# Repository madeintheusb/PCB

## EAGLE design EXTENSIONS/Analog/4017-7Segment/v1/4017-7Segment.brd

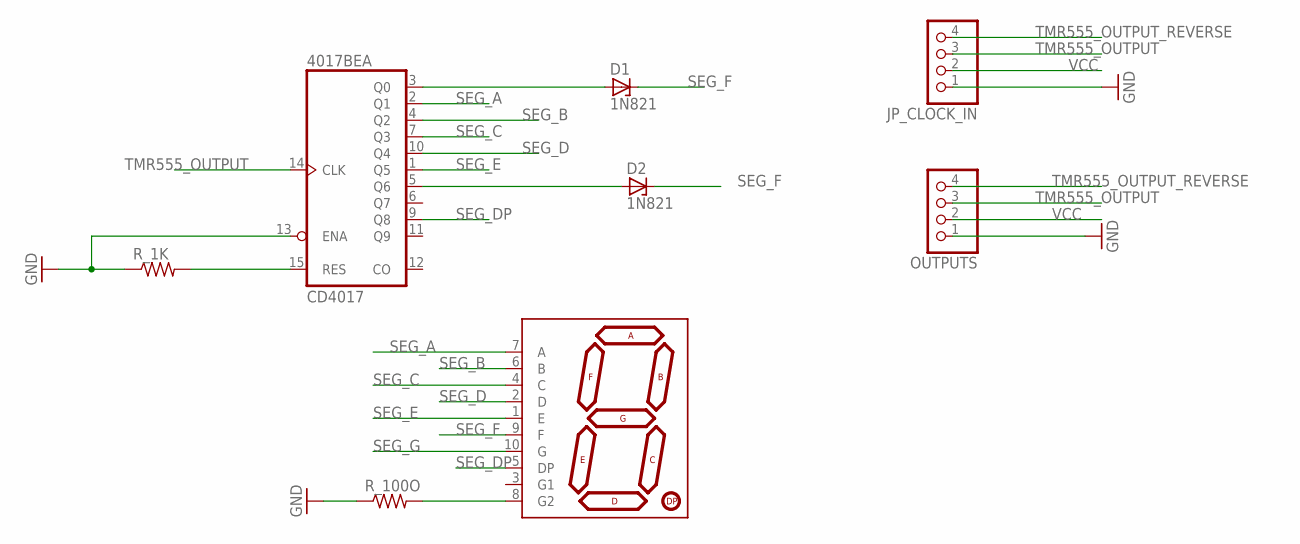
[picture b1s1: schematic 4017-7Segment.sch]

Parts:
4017BE: CD4017; DIL16
D1, D2: 1N821; DO35Z10
JP_CLOCK_IN: PINHD-1X4; 1X04
OUTPUTS: PINHD-1X4; 1X04
R_1K, R_100O: R-US_R1206; R1206
U$1: 7-SEGMENT-DISPLAYPTH; 7-SEGMENT-DISPLAY

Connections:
GND: 4017BE.8 (GND), 4017BE.13 (ENA), JP_CLOCK_IN.1, OUTPUTS.1, R_1K.1, R_100O.1
unnamed: 4017BE.15 (RES), R_1K.2
unnamed: R_100O.2, U$1.8 (G2)
unnamed: 4017BE.3 (Q0), D1.A
unnamed: 4017BE.5 (Q6), D2.A
SEG_A: 4017BE.2 (Q1), U$1.7 (A)
SEG_B: 4017BE.4 (Q2), U$1.6 (B)
SEG_C: 4017BE.7 (Q3), U$1.4 (C)
SEG_D: 4017BE.10 (Q4), U$1.2 (D)
SEG_DP: 4017BE.9 (Q8), U$1.5 (DP)
SEG_E: 4017BE.1 (Q5), U$1.1 (E)
SEG_F: D1.C, D2.C, U$1.9 (F)
SEG_G: U$1.10 (G)
TMR555_OUTPUT: 4017BE.14 (CLK), JP_CLOCK_IN.3, OUTPUTS.3
TMR555_OUTPUT_REVERSE: JP_CLOCK_IN.4, OUTPUTS.4
VCC: 4017BE.16 (VCC), JP_CLOCK_IN.2, OUTPUTS.2

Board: 2 copper layers, 8 parts (0 on the bottom side), 15 nets, no tracks yet.

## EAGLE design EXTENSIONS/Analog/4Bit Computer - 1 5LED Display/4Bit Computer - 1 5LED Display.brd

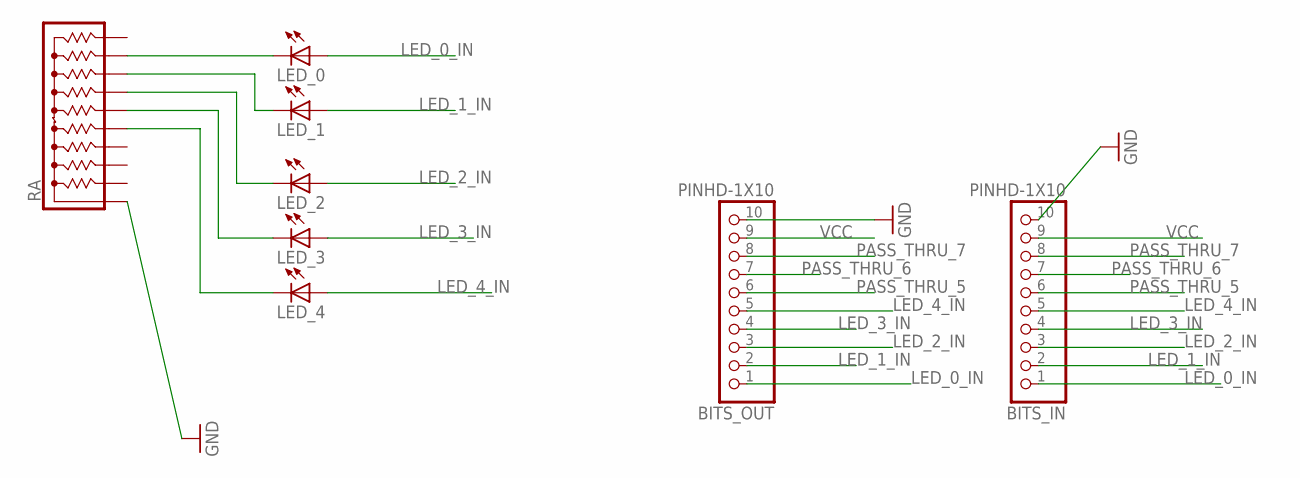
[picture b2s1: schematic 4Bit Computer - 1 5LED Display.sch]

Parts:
BITS_IN: PINHD-1X10; 1X10-BIG
BITS_OUT: PINHD-1X10; 1X10-BIG
LED_0, LED_1, LED_2, LED_3, LED_4: LEDSMT1206; 1206
RA: 4610X; SIP10

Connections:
GND: BITS_IN.10, BITS_OUT.10, RA.1
LED_0_IN: BITS_IN.1, BITS_OUT.1, LED_0.A
LED_1_IN: BITS_IN.2, BITS_OUT.2, LED_1.A
LED_2_IN: BITS_IN.3, BITS_OUT.3, LED_2.A
LED_3_IN: BITS_IN.4, BITS_OUT.4, LED_3.A
LED_4_IN: BITS_IN.5, BITS_OUT.5, LED_4.A
unnamed: LED_0.C, RA.9
unnamed: LED_1.C, RA.8
unnamed: LED_2.C, RA.7
unnamed: LED_3.C, RA.6
unnamed: LED_4.C, RA.5
PASS_THRU_5: BITS_IN.6, BITS_OUT.6
PASS_THRU_6: BITS_IN.7, BITS_OUT.7
PASS_THRU_7: BITS_IN.8, BITS_OUT.8
VCC: BITS_IN.9, BITS_OUT.9

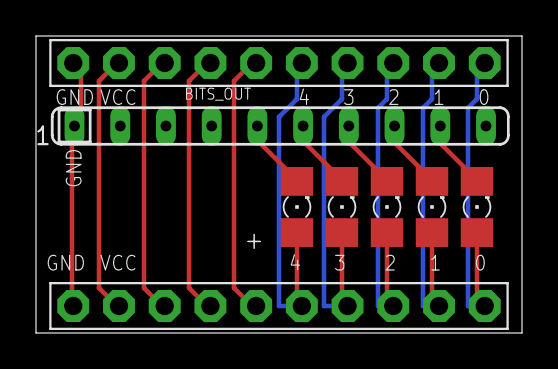
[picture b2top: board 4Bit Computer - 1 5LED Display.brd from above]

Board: 2 copper layers, 27.0 x 16.5 mm, 8 parts (0 on the bottom side), 15 nets.

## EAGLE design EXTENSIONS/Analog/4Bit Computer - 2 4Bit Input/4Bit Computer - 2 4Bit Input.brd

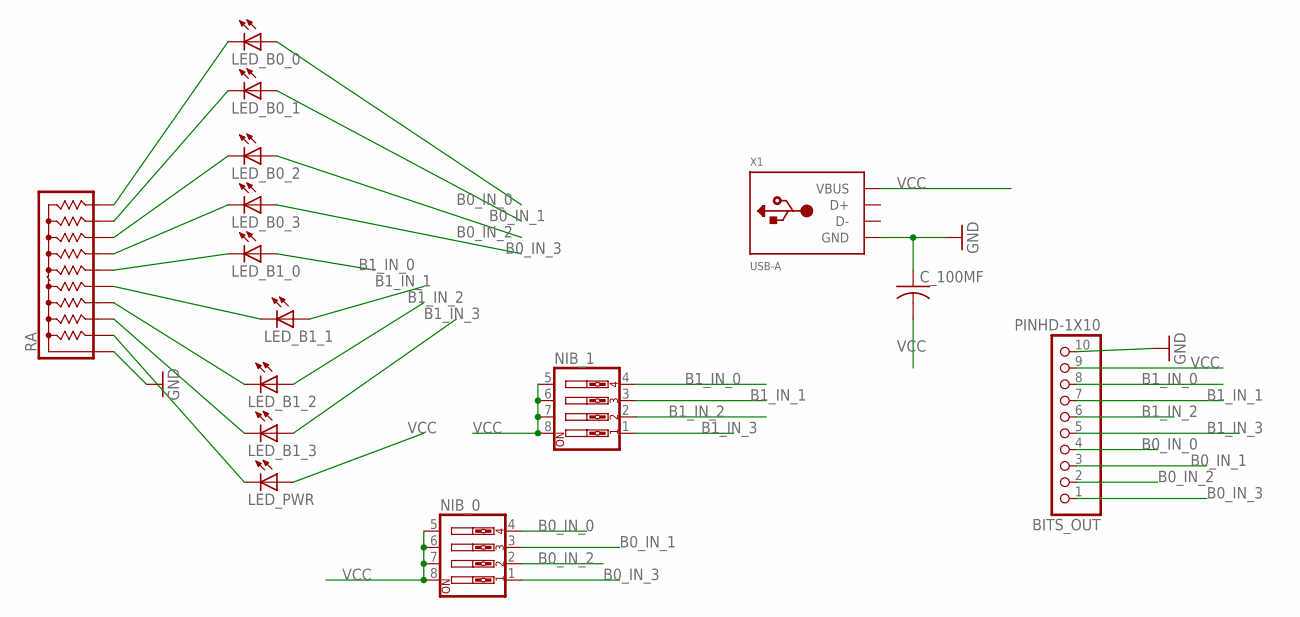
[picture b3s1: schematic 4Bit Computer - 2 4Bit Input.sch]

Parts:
BITS_OUT: PINHD-1X10; 1X10-BIG
C_100MF: C-US025-030X050; C025-030X050
LED_B0_0, LED_B0_1, LED_B0_2, LED_B0_3, LED_B1_0, LED_B1_1, LED_B1_2, LED_B1_3: LEDSMT1206; 1206
LED_PWR: LEDSMT1206; 1206
NIB_0, NIB_1: SW_DIP-4; EDG-04
RA: 4610X; SIP10
X1: USB-A; MOLEX_480371000

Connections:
B0_IN_0: BITS_OUT.4, LED_B0_0.A, NIB_0.4
B0_IN_1: BITS_OUT.3, LED_B0_1.A, NIB_0.3
B0_IN_2: BITS_OUT.2, LED_B0_2.A, NIB_0.2
B0_IN_3: BITS_OUT.1, LED_B0_3.A, NIB_0.1
B1_IN_0: BITS_OUT.8, LED_B1_0.A, NIB_1.4
B1_IN_1: BITS_OUT.7, LED_B1_1.A, NIB_1.3
B1_IN_2: BITS_OUT.6, LED_B1_2.A, NIB_1.2
B1_IN_3: BITS_OUT.5, LED_B1_3.A, NIB_1.1
GND: BITS_OUT.10, C_100MF.1, RA.1, X1.4 (GND)
unnamed: LED_B0_0.C, RA.10
unnamed: LED_B0_1.C, RA.9
unnamed: LED_B0_2.C, RA.8
unnamed: LED_B0_3.C, RA.7
unnamed: LED_B1_0.C, RA.6
unnamed: LED_B1_1.C, RA.5
unnamed: LED_B1_2.C, RA.4
unnamed: LED_B1_3.C, RA.3
unnamed: LED_PWR.C, RA.2
VCC: BITS_OUT.9, C_100MF.2, LED_PWR.A, NIB_0.5, NIB_0.6, NIB_0.7, NIB_0.8, NIB_1.5, NIB_1.6, NIB_1.7, NIB_1.8, X1.1 (VBUS)

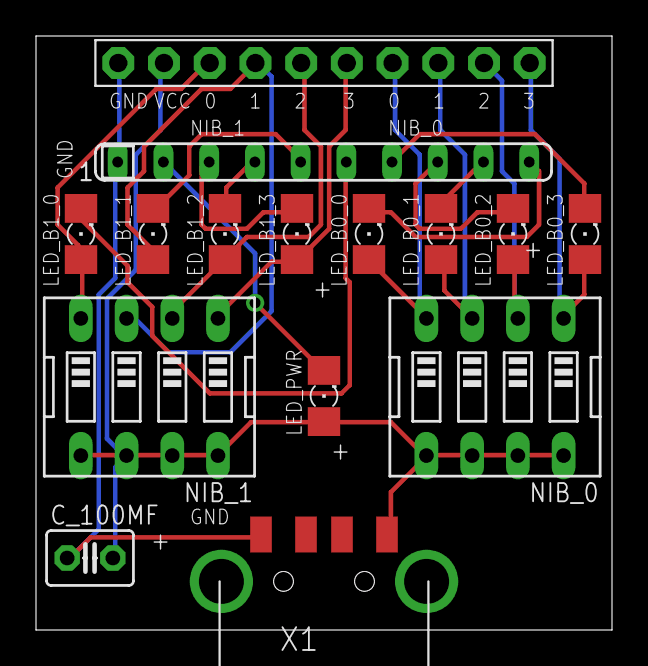
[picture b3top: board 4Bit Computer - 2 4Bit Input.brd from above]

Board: 2 copper layers, 32.0 x 33.0 mm, 15 parts (0 on the bottom side), 19 nets.

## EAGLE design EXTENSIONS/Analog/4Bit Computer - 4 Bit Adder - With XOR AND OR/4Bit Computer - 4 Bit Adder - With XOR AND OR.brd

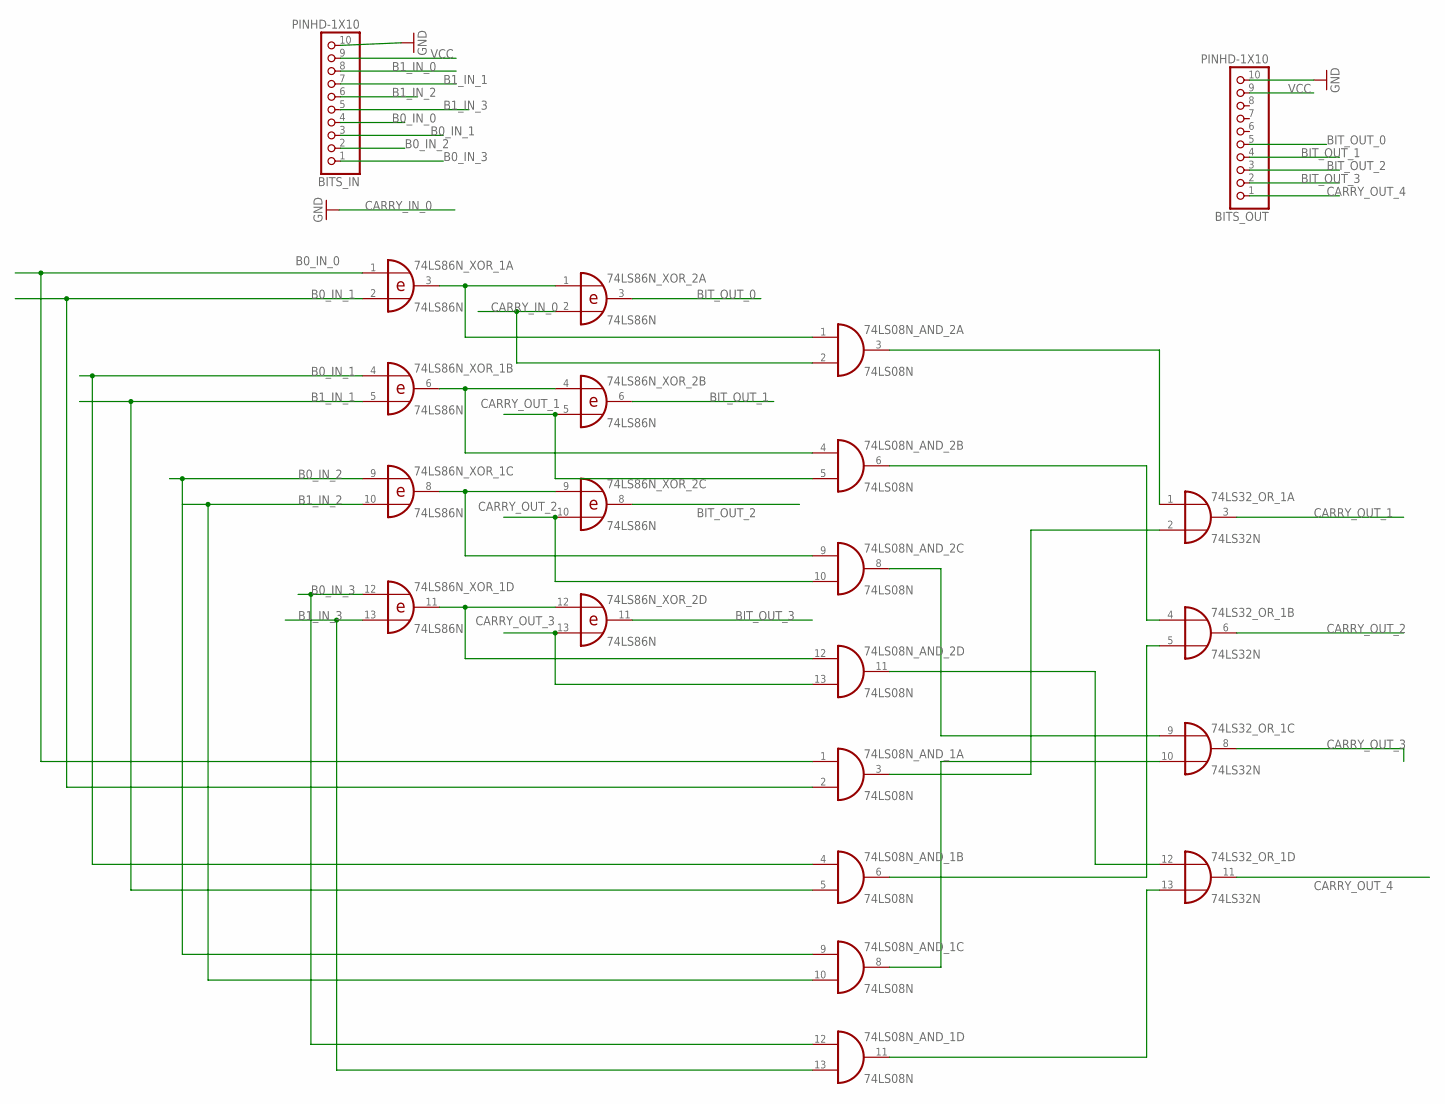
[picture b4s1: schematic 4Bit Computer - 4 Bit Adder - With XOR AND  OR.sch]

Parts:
74LS08N_AND_1, 74LS08N_AND_2: 74LS08N; DIL14
74LS32_OR_1: 74LS32N; DIL14
74LS86N_XOR_1, 74LS86N_XOR_2: 74LS86N; DIL14
BITS_IN: PINHD-1X10; 1X10-BIG
BITS_OUT: PINHD-1X10; 1X10-BIG

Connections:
B0_IN_0: 74LS08N_AND_1.1 (I0), 74LS86N_XOR_1.1 (I0), BITS_IN.4
B0_IN_1: 74LS08N_AND_1.2 (I1), 74LS08N_AND_1.4 (I0), 74LS86N_XOR_1.2 (I1), 74LS86N_XOR_1.4 (I0), BITS_IN.3
B0_IN_2: 74LS08N_AND_1.9 (I0), 74LS86N_XOR_1.9 (I0), BITS_IN.2
B0_IN_3: 74LS08N_AND_1.12 (I0), 74LS86N_XOR_1.12 (I0), BITS_IN.1
B1_IN_0: BITS_IN.8
B1_IN_1: 74LS08N_AND_1.5 (I1), 74LS86N_XOR_1.5 (I1), BITS_IN.7
B1_IN_2: 74LS08N_AND_1.10 (I1), 74LS86N_XOR_1.10 (I1), BITS_IN.6
B1_IN_3: 74LS08N_AND_1.13 (I1), 74LS86N_XOR_1.13 (I1), BITS_IN.5
BIT_OUT_0: 74LS86N_XOR_2.3 (O), BITS_OUT.5
BIT_OUT_1: 74LS86N_XOR_2.6 (O), BITS_OUT.4
BIT_OUT_2: 74LS86N_XOR_2.8 (O), BITS_OUT.3
BIT_OUT_3: 74LS86N_XOR_2.11 (O), BITS_OUT.2
CARRY_IN_0: 74LS08N_AND_2.2 (I1), 74LS86N_XOR_2.2 (I1)
CARRY_OUT_1: 74LS08N_AND_2.5 (I1), 74LS32_OR_1.3 (O), 74LS86N_XOR_2.5 (I1)
CARRY_OUT_2: 74LS08N_AND_2.10 (I1), 74LS32_OR_1.6 (O), 74LS86N_XOR_2.10 (I1)
CARRY_OUT_3: 74LS08N_AND_2.13 (I1), 74LS32_OR_1.8 (O), 74LS86N_XOR_2.13 (I1)
CARRY_OUT_4: 74LS32_OR_1.11 (O), BITS_OUT.1
GND: 74LS08N_AND_1.7 (GND), 74LS08N_AND_2.7 (GND), 74LS32_OR_1.7 (GND), 74LS86N_XOR_1.7 (GND), 74LS86N_XOR_2.7 (GND), BITS_IN.10, BITS_OUT.10
unnamed: 74LS08N_AND_2.1 (I0), 74LS86N_XOR_1.3 (O), 74LS86N_XOR_2.1 (I0)
unnamed: 74LS08N_AND_2.4 (I0), 74LS86N_XOR_1.6 (O), 74LS86N_XOR_2.4 (I0)
unnamed: 74LS08N_AND_2.9 (I0), 74LS86N_XOR_1.8 (O), 74LS86N_XOR_2.9 (I0)
unnamed: 74LS08N_AND_2.12 (I0), 74LS86N_XOR_1.11 (O), 74LS86N_XOR_2.12 (I0)
unnamed: 74LS08N_AND_2.3 (O), 74LS32_OR_1.1 (I0)
unnamed: 74LS08N_AND_1.3 (O), 74LS32_OR_1.2 (I1)
unnamed: 74LS08N_AND_2.6 (O), 74LS32_OR_1.4 (I0)
unnamed: 74LS08N_AND_1.6 (O), 74LS32_OR_1.5 (I1)
unnamed: 74LS08N_AND_2.8 (O), 74LS32_OR_1.9 (I0)
unnamed: 74LS08N_AND_1.8 (O), 74LS32_OR_1.10 (I1)
unnamed: 74LS08N_AND_1.11 (O), 74LS32_OR_1.13 (I1)
unnamed: 74LS08N_AND_2.11 (O), 74LS32_OR_1.12 (I0)
VCC: 74LS08N_AND_1.14 (VCC), 74LS08N_AND_2.14 (VCC), 74LS32_OR_1.14 (VCC), 74LS86N_XOR_1.14 (VCC), 74LS86N_XOR_2.14 (VCC), BITS_IN.9, BITS_OUT.9

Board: 2 copper layers, 7 parts (0 on the bottom side), 30 nets, no tracks yet.

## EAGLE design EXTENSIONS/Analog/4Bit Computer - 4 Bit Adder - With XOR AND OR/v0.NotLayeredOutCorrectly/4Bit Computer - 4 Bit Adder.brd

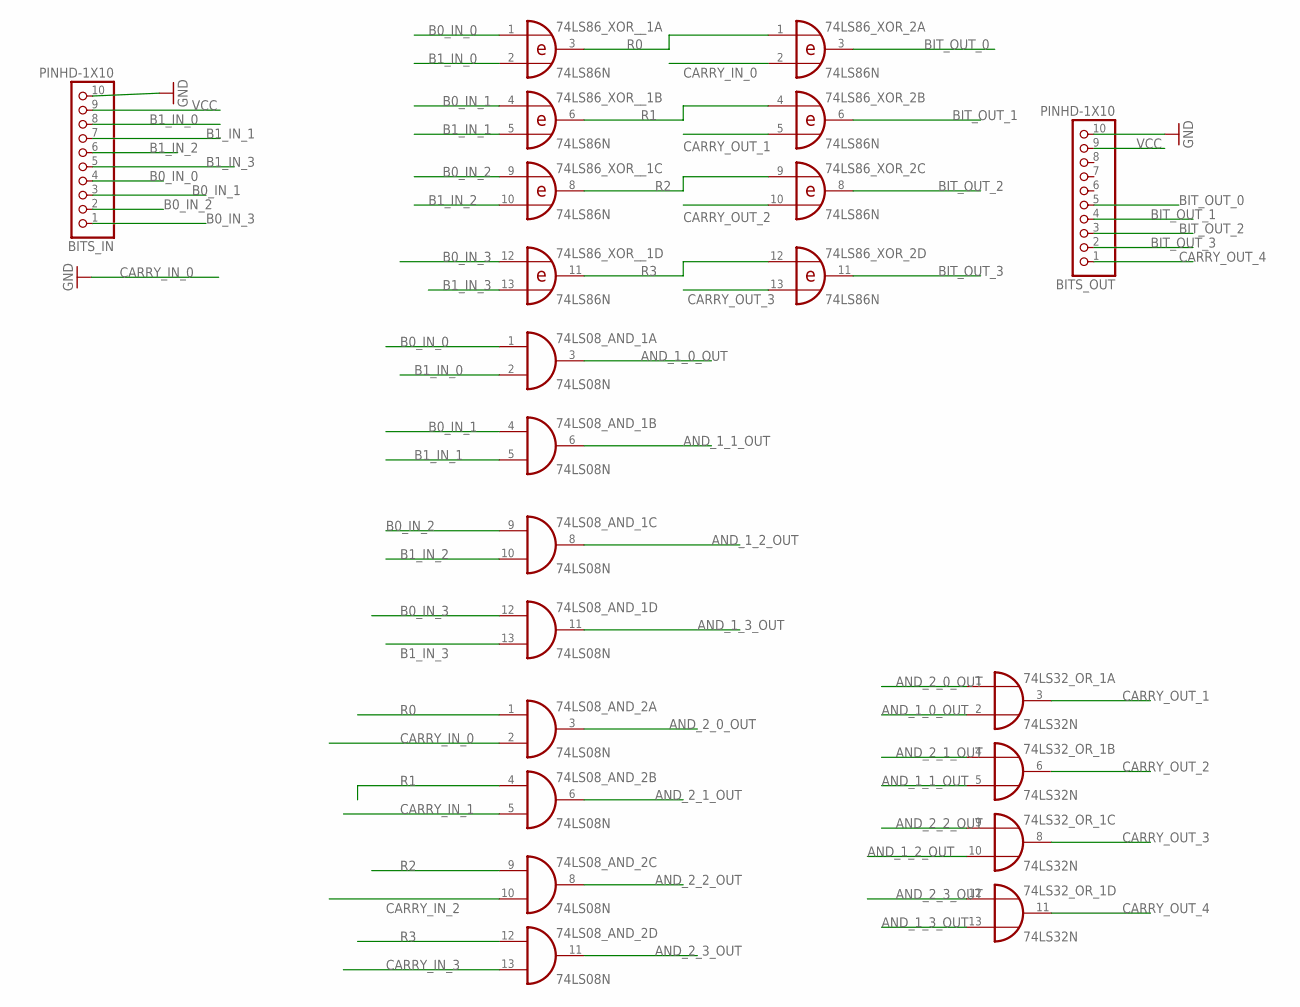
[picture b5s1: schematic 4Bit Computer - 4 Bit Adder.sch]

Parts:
74LS08_AND_1, 74LS08_AND_2: 74LS08N; DIL14
74LS32_OR_1: 74LS32N; DIL14
74LS86_XOR_2, 74LS86_XOR__1: 74LS86N; DIL14
BITS_IN: PINHD-1X10; 1X10-BIG
BITS_OUT: PINHD-1X10; 1X10-BIG

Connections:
AND_1_0_OUT: 74LS08_AND_1.3 (O), 74LS32_OR_1.2 (I1)
AND_1_1_OUT: 74LS08_AND_1.6 (O), 74LS32_OR_1.5 (I1)
AND_1_2_OUT: 74LS08_AND_1.8 (O), 74LS32_OR_1.10 (I1)
AND_1_3_OUT: 74LS08_AND_1.11 (O), 74LS32_OR_1.13 (I1)
AND_2_0_OUT: 74LS08_AND_2.3 (O), 74LS32_OR_1.1 (I0)
AND_2_1_OUT: 74LS08_AND_2.6 (O), 74LS32_OR_1.4 (I0)
AND_2_2_OUT: 74LS08_AND_2.8 (O), 74LS32_OR_1.9 (I0)
AND_2_3_OUT: 74LS08_AND_2.11 (O), 74LS32_OR_1.12 (I0)
B0_IN_0: 74LS08_AND_1.1 (I0), 74LS86_XOR__1.1 (I0), BITS_IN.4
B0_IN_1: 74LS08_AND_1.4 (I0), 74LS86_XOR__1.4 (I0), BITS_IN.3
B0_IN_2: 74LS08_AND_1.9 (I0), 74LS86_XOR__1.9 (I0), BITS_IN.2
B0_IN_3: 74LS08_AND_1.12 (I0), 74LS86_XOR__1.12 (I0), BITS_IN.1
B1_IN_0: 74LS08_AND_1.2 (I1), 74LS86_XOR__1.2 (I1), BITS_IN.8
B1_IN_1: 74LS08_AND_1.5 (I1), 74LS86_XOR__1.5 (I1), BITS_IN.7
B1_IN_2: 74LS08_AND_1.10 (I1), 74LS86_XOR__1.10 (I1), BITS_IN.6
B1_IN_3: 74LS08_AND_1.13 (I1), 74LS86_XOR__1.13 (I1), BITS_IN.5
BIT_OUT_0: 74LS86_XOR_2.3 (O), BITS_OUT.5
BIT_OUT_1: 74LS86_XOR_2.6 (O), BITS_OUT.4
BIT_OUT_2: 74LS86_XOR_2.8 (O), BITS_OUT.3
BIT_OUT_3: 74LS86_XOR_2.11 (O), BITS_OUT.2
CARRY_IN_0: 74LS08_AND_2.2 (I1), 74LS86_XOR_2.2 (I1)
CARRY_IN_1: 74LS08_AND_2.5 (I1)
CARRY_IN_2: 74LS08_AND_2.10 (I1)
CARRY_IN_3: 74LS08_AND_2.13 (I1)
CARRY_OUT_1: 74LS32_OR_1.3 (O), 74LS86_XOR_2.5 (I1)
CARRY_OUT_2: 74LS32_OR_1.6 (O), 74LS86_XOR_2.10 (I1)
CARRY_OUT_3: 74LS32_OR_1.8 (O), 74LS86_XOR_2.13 (I1)
CARRY_OUT_4: 74LS32_OR_1.11 (O), BITS_OUT.1
GND: 74LS08_AND_1.7 (GND), 74LS08_AND_2.7 (GND), 74LS32_OR_1.7 (GND), 74LS86_XOR_2.7 (GND), 74LS86_XOR__1.7 (GND), BITS_IN.10, BITS_OUT.10
R0: 74LS08_AND_2.1 (I0), 74LS86_XOR_2.1 (I0), 74LS86_XOR__1.3 (O)
R1: 74LS08_AND_2.4 (I0), 74LS86_XOR_2.4 (I0), 74LS86_XOR__1.6 (O)
R2: 74LS08_AND_2.9 (I0), 74LS86_XOR_2.9 (I0), 74LS86_XOR__1.8 (O)
R3: 74LS08_AND_2.12 (I0), 74LS86_XOR_2.12 (I0), 74LS86_XOR__1.11 (O)
VCC: 74LS08_AND_1.14 (VCC), 74LS08_AND_2.14 (VCC), 74LS32_OR_1.14 (VCC), 74LS86_XOR_2.14 (VCC), 74LS86_XOR__1.14 (VCC), BITS_IN.9, BITS_OUT.9

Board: 2 copper layers, 7 parts (0 on the bottom side), 31 nets, no tracks yet.

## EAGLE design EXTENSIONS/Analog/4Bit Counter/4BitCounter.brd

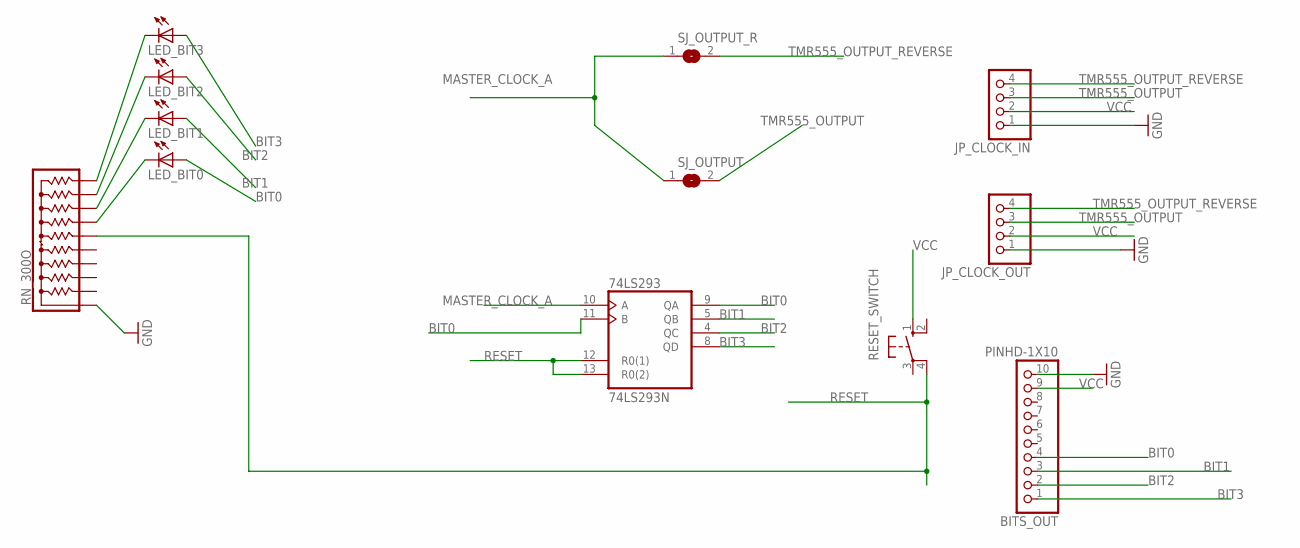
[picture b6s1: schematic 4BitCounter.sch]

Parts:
74LS293: 74LS293N; DIL14
BITS_OUT: PINHD-1X10; 1X10-BIG
JP_CLOCK_IN: PINHD-1X4; 1X04
JP_CLOCK_OUT: PINHD-1X4; 1X04
LED_BIT0, LED_BIT1, LED_BIT2, LED_BIT3: LEDSMT1206; 1206
RESET_SWITCH: 10-XX; B3F-10XX
RN_300O: 4610X; SIP10
SJ_OUTPUT: SOLDERJUMPERREFLOW; SOLDERJUMPER_REFLOW
SJ_OUTPUT_R: SOLDERJUMPERREFLOW; SOLDERJUMPER_REFLOW

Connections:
BIT0: 74LS293.9 (QA), 74LS293.11 (B), BITS_OUT.4, LED_BIT0.A
BIT1: 74LS293.5 (QB), BITS_OUT.3, LED_BIT1.A
BIT2: 74LS293.4 (QC), BITS_OUT.2, LED_BIT2.A
BIT3: 74LS293.8 (QD), BITS_OUT.1, LED_BIT3.A
GND: 74LS293.7 (GND), BITS_OUT.10, JP_CLOCK_IN.1, JP_CLOCK_OUT.1, RN_300O.1
MASTER_CLOCK_A: 74LS293.10 (A), SJ_OUTPUT.1, SJ_OUTPUT_R.1
unnamed: LED_BIT1.C, RN_300O.8
unnamed: LED_BIT0.C, RN_300O.7
unnamed: LED_BIT2.C, RN_300O.9
unnamed: LED_BIT3.C, RN_300O.10
RESET: 74LS293.12 (R0(1)), 74LS293.13 (R0(2)), RESET_SWITCH.4 (P1), RN_300O.6
TMR555_OUTPUT: JP_CLOCK_IN.3, JP_CLOCK_OUT.3, SJ_OUTPUT.2
TMR555_OUTPUT_REVERSE: JP_CLOCK_IN.4, JP_CLOCK_OUT.4, SJ_OUTPUT_R.2
VCC: 74LS293.14 (VCC), BITS_OUT.9, JP_CLOCK_IN.2, JP_CLOCK_OUT.2, RESET_SWITCH.1 (S)

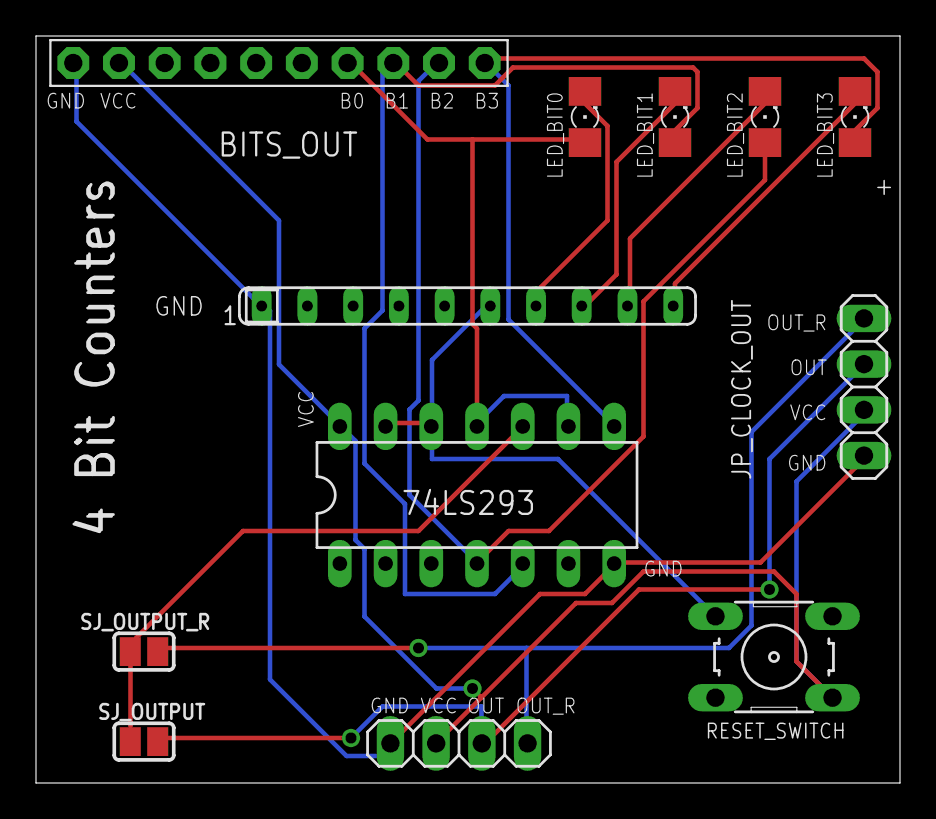
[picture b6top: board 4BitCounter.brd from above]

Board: 2 copper layers, 48.0 x 41.5 mm, 12 parts (0 on the bottom side), 14 nets.

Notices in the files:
parts and their libraries:
SparkFun-DigitalIC: Licensing: Creative Commons ShareAlike 4.0 International - https://creativecommons.org/licenses/by-sa/4.0
microbuilder: This work is placed in the public domain, and may be freely used for commercial and non-commercial work with the following conditions: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
